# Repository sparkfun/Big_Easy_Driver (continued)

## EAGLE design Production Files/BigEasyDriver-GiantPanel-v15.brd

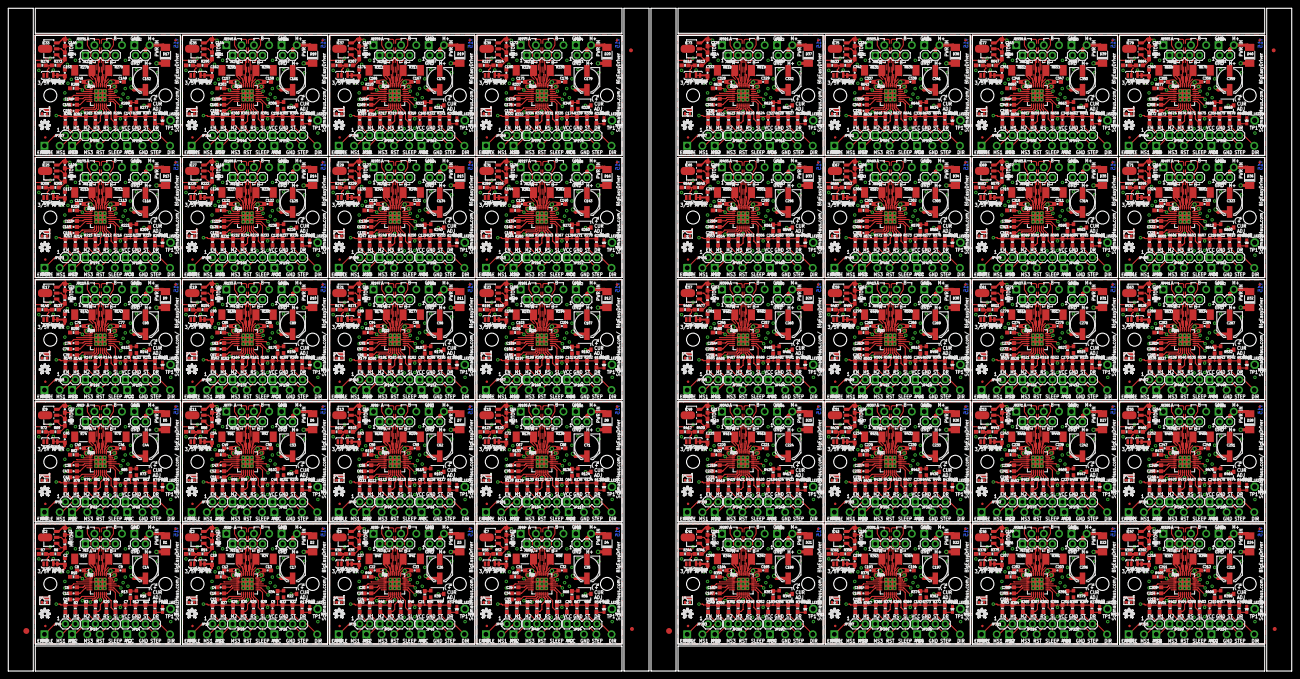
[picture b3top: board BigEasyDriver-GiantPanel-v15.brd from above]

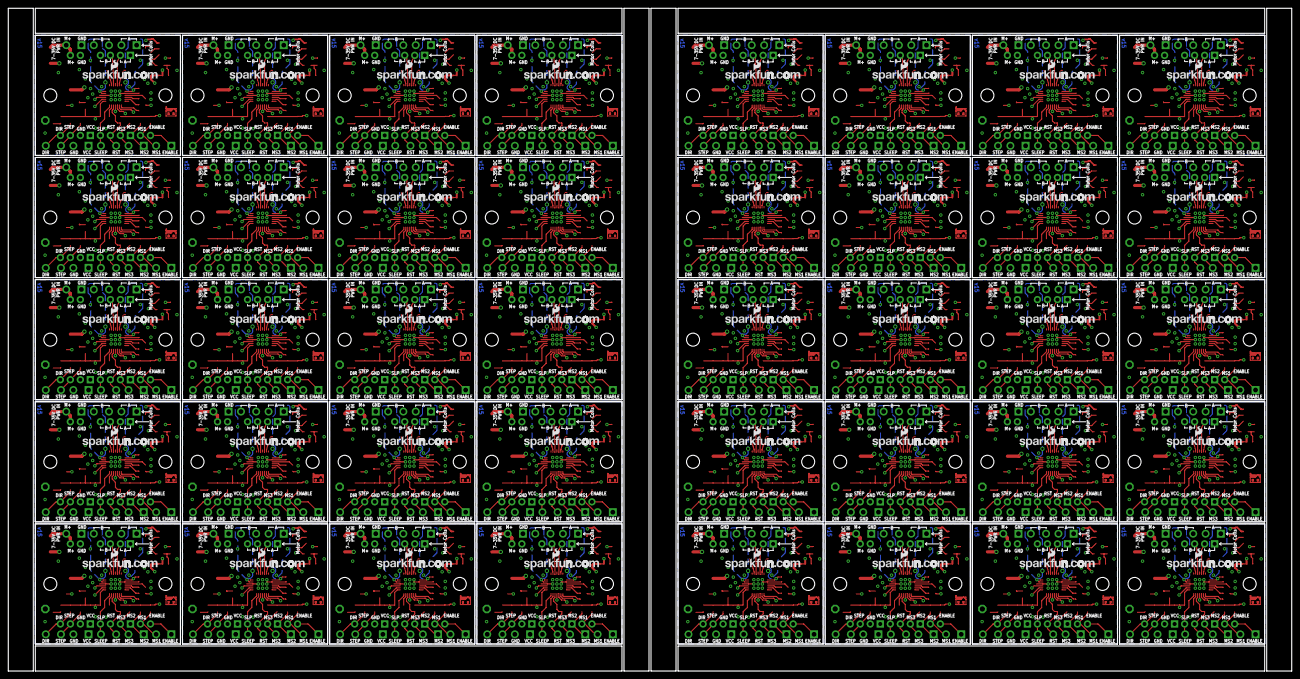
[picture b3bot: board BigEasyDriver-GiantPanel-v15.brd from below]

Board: 2 copper layers, 325.6 x 168.1 mm, 2126 parts (40 on the bottom side), 1280 nets.

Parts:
3/5V, 3/5V1, 3/5V2, 3/5V3, 3/5V4, 3/5V5, 3/5V6, 3/5V7, 3/5V8, 3/5V9, 3/5V10, 3/5V11, 3/5V12, 3/5V13, 3/5V14, 3/5V15, 3/5V16, 3/5V17, 3/5V18, 3/5V19, 3/5V20, 3/5V21, 3/5V22, 3/5V23, 3/5V24, 3/5V25, 3/5V26, 3/5V27, 3/5V28, 3/5V29, 3/5V30, 3/5V31, 3/5V32, 3/5V33, 3/5V34, 3/5V35, 3/5V36, 3/5V37, 3/5V38, 3/5V39: SOLDERJUMPERNO; SJ_2S-NO
APWR, APWR1, APWR2, APWR3, APWR4, APWR5, APWR6, APWR7, APWR8, APWR9, APWR10, APWR11, APWR12, APWR13, APWR14, APWR15, APWR16, APWR17, APWR18, APWR19, APWR20, APWR21, APWR22, APWR23, APWR24, APWR25, APWR26, APWR27, APWR28, APWR29, APWR30, APWR31, APWR32, APWR33, APWR34, APWR35, APWR36, APWR37, APWR38, APWR39: SOLDERJUMPERTRACE; SJ_2S-TRACE
C1, C3, C19, C28, C37, C46, C55, C64, C73, C82, C91, C100, C109, C118, C127, C136, C145, C154, C163, C172, C181, C190, C199, C208, C217, C226, C235, C244, C253, C262, C271, C280, C289, C298, C307, C316, C325, C334, C343, C352: .1uF; 0603-CAP
C2, C18, C27, C36, C45, C54, C63, C72, C81, C90, C99, C108, C117, C126, C135, C144, C153, C162, C171, C180, C189, C198, C207, C216, C225, C234, C243, C252, C261, C270, C279, C288, C297, C306, C315, C324, C333, C342, C351, C360: 1uF; 0603-CAP
C4, C5, C6, C7, C8, C9, C11, C12, C13, C16, C20, C21, C22, C23, C25, C29, C30, C31, C32, C34, C38, C39, C40, C41, C43, C47, C48, C49, C50, C52, C56, C57, C58, C59, C61, C65, C66, C67, C68, C70, C74, C75, C76, C77, C79, C83, C84, C85, C86, C88, C92, C93, C94, C95, C97, C101, C102, C103, C104, C106, C110, C111, C112, C113, C115, C119, C120, C121, C122, C124, C128, C129, C130, C131, C133, C137, C138, C139, C140, C142, C146, C147, C148, C149, C151, C155, C156, C157, C158, C160, C164, C165, C166, C167, C169, C173, C174, C175, C176, C178, C182, C183, C184, C185, C187, C191, C192, C193, C194, C196, C200, C201, C202, C203, C205, C209, C210, C211, C212, C214, C218, C219, C220, C221, C223, C227, C228, C229, C230, C232, C236, C237, C238, C239, C241, C245, C246, C247, C248, C250, C254, C255, C256, C257, C259, C263, C264, C265, C266, C268, C272, C273, C274, C275, C277, C281, C282, C283, C284, C286, C290, C291, C292, C293, C295, C299, C300, C301, C302, C304, C308, C309, C310, C311, C313, C317, C318, C319, C320, C322, C326, C327, C328, C329, C331, C335, C336, C337, C338, C340, C344, C345, C346, C347, C349, C353, C354, C355, C356, C358: .1uf; 0603-CAP
C10, C15, C24, C33, C42, C51, C60, C69, C78, C87, C96, C105, C114, C123, C132, C141, C150, C159, C168, C177, C186, C195, C204, C213, C222, C231, C240, C249, C258, C267, C276, C285, C294, C303, C312, C321, C330, C339, C348, C357: .22uF; 0603-CAP
C14, C17, C26, C35, C44, C53, C62, C71, C80, C89, C98, C107, C116, C125, C134, C143, C152, C161, C170, C179, C188, C197, C206, C215, C224, C233, C242, C251, C260, C269, C278, C287, C296, C305, C314, C323, C332, C341, C350, C359: 47uF; PANASONIC_D
D1, D2, D3, D4, D5, D6, D7, D8, D9, D10, D11, D12, D13, D14, D15, D16, D17, D18, D19, D20, D21, D22, D23, D24, D25, D26, D27, D28, D29, D30, D31, D32, D33, D34, D35, D36, D37, D38, D39, D40: B340A-13-F; DO-214AC
E$1, E$5: FIDUCIAL-1.5X3
E$2, E$3, E$4, E$6: FIDUCIAL-1X2
IC1, IC4, IC6, IC8, IC10, IC12, IC14, IC16, IC18, IC20, IC22, IC24, IC26, IC28, IC30, IC32, IC34, IC36, IC38, IC40, IC42, IC44, IC46, IC48, IC50, IC52, IC54, IC56, IC58, IC60, IC62, IC64, IC66, IC68, IC70, IC72, IC74, IC76, IC78, IC80: A4983ALT1; QFN-28-5MM_ALT1
IC2, IC3, IC5, IC7, IC9, IC11, IC13, IC15, IC17, IC19, IC21, IC23, IC25, IC27, IC29, IC31, IC33, IC35, IC37, IC39, IC41, IC43, IC45, IC47, IC49, IC51, IC53, IC55, IC57, IC59, IC61, IC63, IC65, IC67, IC69, IC71, IC73, IC75, IC77, IC79: LM317L; SCHMALZHAUS_SOT89
JP1, JP6, JP17, JP19, JP31, JP33, JP45, JP47, JP59, JP61, JP73, JP75, JP87, JP89, JP101, JP103, JP115, JP117, JP129, JP131, JP143, JP145, JP157, JP159, JP171, JP173, JP185, JP187, JP199, JP201, JP213, JP215, JP227, JP229, JP241, JP243, JP255, JP257, JP269, JP271, JP283, JP285, JP297, JP299, JP311, JP313, JP325, JP327, JP339, JP341, JP353, JP355, JP367, JP369, JP381, JP383, JP395, JP397, JP409, JP411, JP423, JP425, JP437, JP439, JP451, JP453, JP465, JP467, JP479, JP481, JP493, JP495, JP507, JP509, JP521, JP523, JP535, JP537, JP549, JP551: 1X02
JP2, JP4, JP27, JP28, JP41, JP42, JP55, JP56, JP69, JP70, JP83, JP84, JP97, JP98, JP111, JP112, JP125, JP126, JP139, JP140, JP153, JP154, JP167, JP168, JP181, JP182, JP195, JP196, JP209, JP210, JP223, JP224, JP237, JP238, JP251, JP252, JP265, JP266, JP279, JP280, JP293, JP294, JP307, JP308, JP321, JP322, JP335, JP336, JP349, JP350, JP363, JP364, JP377, JP378, JP391, JP392, JP405, JP406, JP419, JP420, JP433, JP434, JP447, JP448, JP461, JP462, JP475, JP476, JP489, JP490, JP503, JP504, JP517, JP518, JP531, JP532, JP545, JP546, JP559, JP560: FIDUCIAL1X2.5; FIDUCIAL-1X2.5
JP3, JP10, JP14, JP18, JP20, JP26, JP32, JP34, JP40, JP46, JP48, JP54, JP60, JP62, JP68, JP74, JP76, JP82, JP88, JP90, JP96, JP102, JP104, JP110, JP116, JP118, JP124, JP130, JP132, JP138, JP144, JP146, JP152, JP158, JP160, JP166, JP172, JP174, JP180, JP186, JP188, JP194, JP200, JP202, JP208, JP214, JP216, JP222, JP228, JP230, JP236, JP242, JP244, JP250, JP256, JP258, JP264, JP270, JP272, JP278, JP284, JP286, JP292, JP298, JP300, JP306, JP312, JP314, JP320, JP326, JP328, JP334, JP340, JP342, JP348, JP354, JP356, JP362, JP368, JP370, JP376, JP382, JP384, JP390, JP396, JP398, JP404, JP410, JP412, JP418, JP424, JP426, JP432, JP438, JP440, JP446, JP452, JP454, JP460, JP466, JP468, JP474, JP480, JP482, JP488, JP494, JP496, JP502, JP508, JP510, JP516, JP522, JP524, JP530, JP536, JP538, JP544, JP550, JP552, JP558: 1X04
JP5, JP11, JP12, JP21, JP23, JP24, JP35, JP37, JP38, JP49, JP51, JP52, JP63, JP65, JP66, JP77, JP79, JP80, JP91, JP93, JP94, JP105, JP107, JP108, JP119, JP121, JP122, JP133, JP135, JP136, JP147, JP149, JP150, JP161, JP163, JP164, JP175, JP177, JP178, JP189, JP191, JP192, JP203, JP205, JP206, JP217, JP219, JP220, JP231, JP233, JP234, JP245, JP247, JP248, JP259, JP261, JP262, JP273, JP275, JP276, JP287, JP289, JP290, JP301, JP303, JP304, JP315, JP317, JP318, JP329, JP331, JP332, JP343, JP345, JP346, JP357, JP359, JP360, JP371, JP373, JP374, JP385, JP387, JP388, JP399, JP401, JP402, JP413, JP415, JP416, JP427, JP429, JP430, JP441, JP443, JP444, JP455, JP457, JP458, JP469, JP471, JP472, JP483, JP485, JP486, JP497, JP499, JP500, JP511, JP513, JP514, JP525, JP527, JP528, JP539, JP541, JP542, JP553, JP555, JP556: SCREWTERMINAL-3.5MM-4_LOCK
JP7, JP13, JP22, JP25, JP36, JP39, JP50, JP53, JP64, JP67, JP78, JP81, JP92, JP95, JP106, JP109, JP120, JP123, JP134, JP137, JP148, JP151, JP162, JP165, JP176, JP179, JP190, JP193, JP204, JP207, JP218, JP221, JP232, JP235, JP246, JP249, JP260, JP263, JP274, JP277, JP288, JP291, JP302, JP305, JP316, JP319, JP330, JP333, JP344, JP347, JP358, JP361, JP372, JP375, JP386, JP389, JP400, JP403, JP414, JP417, JP428, JP431, JP442, JP445, JP456, JP459, JP470, JP473, JP484, JP487, JP498, JP501, JP512, JP515, JP526, JP529, JP540, JP543, JP554, JP557: SCREWTERMINAL-3.5MM-2_LOCK
JP8, JP9, JP15, JP16, JP29, JP30, JP43, JP44, JP57, JP58, JP71, JP72, JP85, JP86, JP99, JP100, JP113, JP114, JP127, JP128, JP141, JP142, JP155, JP156, JP169, JP170, JP183, JP184, JP197, JP198, JP211, JP212, JP225, JP226, JP239, JP240, JP253, JP254, JP267, JP268, JP281, JP282, JP295, JP296, JP309, JP310, JP323, JP324, JP337, JP338, JP351, JP352, JP365, JP366, JP379, JP380, JP393, JP394, JP407, JP408, JP421, JP422, JP435, JP436, JP449, JP450, JP463, JP464, JP477, JP478, JP491, JP492, JP505, JP506, JP519, JP520, JP533, JP534, JP547, JP548: STAND-OFF
LOGO1, LOGO2, LOGO3, LOGO4, LOGO5, LOGO6, LOGO7, LOGO8, LOGO9, LOGO10, LOGO11, LOGO12, LOGO13, LOGO14, LOGO15, LOGO16, LOGO17, LOGO18, LOGO19, LOGO20, LOGO21, LOGO22, LOGO23, LOGO24, LOGO25, LOGO26, LOGO27, LOGO28, LOGO29, LOGO30, LOGO31, LOGO32, LOGO33, LOGO34, LOGO35, LOGO36, LOGO37, LOGO38, LOGO39, LOGO40: OSHW_LOGO_FILLX0100-NT; OSHW_FILLX100_NOTEXT
PWR_LED, PWR_LED1, PWR_LED2, PWR_LED3, PWR_LED4, PWR_LED5, PWR_LED6, PWR_LED7, PWR_LED8, PWR_LED9, PWR_LED10, PWR_LED11, PWR_LED12, PWR_LED13, PWR_LED14, PWR_LED15, PWR_LED16, PWR_LED17, PWR_LED18, PWR_LED19, PWR_LED20, PWR_LED21, PWR_LED22, PWR_LED23, PWR_LED24, PWR_LED25, PWR_LED26, PWR_LED27, PWR_LED28, PWR_LED29, PWR_LED30, PWR_LED31, PWR_LED32, PWR_LED33, PWR_LED34, PWR_LED35, PWR_LED36, PWR_LED37, PWR_LED38, PWR_LED39: YELLOW; LED-0603
R1, R2, R3, R4, R5, R10, R11, R12, R20, R25, R26, R27, R28, R29, R30, R31, R32, R33, R42, R43, R44, R45, R46, R47, R48, R49, R50, R59, R60, R61, R62, R63, R64, R65, R66, R67, R76, R77, R78, R79, R80, R81, R82, R83, R84, R93, R94, R95, R96, R97, R98, R99, R100, R101, R110, R111, R112, R113, R114, R115, R116, R117, R118, R127, R128, R129, R130, R131, R132, R133, R134, R135, R144, R145, R146, R147, R148, R149, R150, R151, R152, R161, R162, R163, R164, R165, R166, R167, R168, R169, R178, R179, R180, R181, R182, R183, R184, R185, R186, R195, R196, R197, R198, R199, R200, R201, R202, R203, R212, R213, R214, R215, R216, R217, R218, R219, R220, R229, R230, R231, R232, R233, R234, R235, R236, R237, R246, R247, R248, R249, R250, R251, R252, R253, R254, R263, R264, R265, R266, R267, R268, R269, R270, R271, R280, R281, R282, R283, R284, R285, R286, R287, R288, R297, R298, R299, R300, R301, R302, R303, R304, R305, R314, R315, R316, R317, R318, R319, R320, R321, R322, R331, R332, R333, R334, R335, R336, R337, R338, R339, R348, R349, R350, R351, R352, R353, R354, R355, R356, R365, R366, R367, R368, R369, R370, R371, R372, R373, R382, R383, R384, R385, R386, R387, R388, R389, R390, R399, R400, R401, R402, R403, R404, R405, R406, R407, R416, R417, R418, R419, R420, R421, R422, R423, R424, R433, R434, R435, R436, R437, R438, R439, R440, R441, R450, R451, R452, R453, R454, R455, R456, R457, R458, R467, R468, R469, R470, R471, R472, R473, R474, R475, R484, R485, R486, R487, R488, R489, R490, R491, R492, R501, R502, R503, R504, R505, R506, R507, R508, R509, R518, R519, R520, R521, R522, R523, R524, R525, R526, R535, R536, R537, R538, R539, R540, R541, R542, R543, R552, R553, R554, R555, R556, R557, R558, R559, R560, R569, R570, R571, R572, R573, R574, R575, R576, R577, R586, R587, R588, R589, R590, R591, R592, R593, R594, R603, R604, R605, R606, R607, R608, R609, R610, R611, R620, R621, R622, R623, R624, R625, R626, R627, R628, R637, R638, R639, R640, R641, R642, R643, R644, R645, R654, R655, R656, R657, R658, R659, R660, R661, R662, R671, R672, R673, R674, R675, R676, R677, R678, R679: 20K; 0603-RES
R6, R14, R35, R52, R69, R86, R103, R120, R137, R154, R171, R188, R205, R222, R239, R256, R273, R290, R307, R324, R341, R358, R375, R392, R409, R426, R443, R460, R477, R494, R511, R528, R545, R562, R579, R596, R613, R630, R647, R664: 390; 0603-RES
R7, R21, R38, R55, R72, R89, R106, R123, R140, R157, R174, R191, R208, R225, R242, R259, R276, R293, R310, R327, R344, R361, R378, R395, R412, R429, R446, R463, R480, R497, R514, R531, R548, R565, R582, R599, R616, R633, R650, R667: 330; 0603-RES
R8, R15, R36, R53, R70, R87, R104, R121, R138, R155, R172, R189, R206, R223, R240, R257, R274, R291, R308, R325, R342, R359, R376, R393, R410, R427, R444, R461, R478, R495, R512, R529, R546, R563, R580, R597, R614, R631, R648, R665: 240; 0603-RES
R9, R17, R37, R54, R71, R88, R105, R122, R139, R156, R173, R190, R207, R224, R241, R258, R275, R292, R309, R326, R343, R360, R377, R394, R411, R428, R445, R462, R479, R496, R513, R530, R547, R564, R581, R598, R615, R632, R649, R666: 1K; 0603-RES
R13, R34, R51, R68, R85, R102, R119, R136, R153, R170, R187, R204, R221, R238, R255, R272, R289, R306, R323, R340, R357, R374, R391, R408, R425, R442, R459, R476, R493, R510, R527, R544, R561, R578, R595, R612, R629, R646, R663, R680: 2.49K; 0603-RES
R16, R22, R39, R56, R73, R90, R107, R124, R141, R158, R175, R192, R209, R226, R243, R260, R277, R294, R311, R328, R345, R362, R379, R396, R413, R430, R447, R464, R481, R498, R515, R532, R549, R566, R583, R600, R617, R634, R651, R668: 10K; TRIMPOT-3MM
R18, R19, R23, R24, R40, R41, R57, R58, R74, R75, R91, R92, R108, R109, R125, R126, R142, R143, R159, R160, R176, R177, R193, R194, R210, R211, R227, R228, R244, R245, R261, R262, R278, R279, R295, R296, R312, R313, R329, R330, R346, R347, R363, R364, R380, R381, R397, R398, R414, R415, R431, R432, R448, R449, R465, R466, R482, R483, R499, R500, R516, R517, R533, R534, R550, R551, R567, R568, R584, R585, R601, R602, R618, R619, R635, R636, R652, R653, R669, R670: .11; R2010
TP1, TP2, TP3, TP4, TP5, TP6, TP7, TP8, TP9, TP10, TP11, TP12, TP13, TP14, TP15, TP16, TP17, TP18, TP19, TP20, TP21, TP22, TP23, TP24, TP25, TP26, TP27, TP28, TP29, TP30, TP31, TP32, TP33, TP34, TP35, TP36, TP37, TP38, TP39, TP40: TPPAD1-13; P1-13
U$1, U$6, U$11, U$16, U$21, U$26, U$31, U$36, U$41, U$46, U$51, U$56, U$61, U$66, U$71, U$76, U$81, U$86, U$91, U$96, U$101, U$106, U$111, U$116, U$121, U$126, U$131, U$136, U$141, U$146, U$151, U$156, U$161, U$166, U$171, U$176, U$181, U$186, U$191, U$196: SCHMALZHAUS_SMALL
U$2, U$7, U$12, U$17, U$22, U$27, U$32, U$37, U$42, U$47, U$52, U$57, U$62, U$67, U$72, U$77, U$82, U$87, U$92, U$97, U$102, U$107, U$112, U$117, U$122, U$127, U$132, U$137, U$142, U$147, U$152, U$157, U$162, U$167, U$172, U$177, U$182, U$187, U$192, U$197: LOGO-SFENEW; SFE-NEW-WEBLOGO
U$3, U$4, U$5, U$8, U$9, U$10, U$13, U$14, U$15, U$18, U$19, U$20, U$23, U$24, U$25, U$28, U$29, U$30, U$33, U$34, U$35, U$38, U$39, U$40, U$43, U$44, U$45, U$48, U$49, U$50, U$53, U$54, U$55, U$58, U$59, U$60, U$63, U$64, U$65, U$68, U$69, U$70, U$73, U$74, U$75, U$78, U$79, U$80, U$83, U$84, U$85, U$88, U$89, U$90, U$93, U$94, U$95, U$98, U$99, U$100, U$103, U$104, U$105, U$108, U$109, U$110, U$113, U$114, U$115, U$118, U$119, U$120, U$123, U$124, U$125, U$128, U$129, U$130, U$133, U$134, U$135, U$138, U$139, U$140, U$143, U$144, U$145, U$148, U$149, U$150, U$153, U$154, U$155, U$158, U$159, U$160, U$163, U$164, U$165, U$168, U$169, U$170, U$173, U$174, U$175, U$178, U$179, U$180, U$183, U$184, U$185, U$188, U$189, U$190, U$193, U$194, U$195, U$198, U$199, U$200: PAD; PAD-0.008

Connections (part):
5V_ALT: APWR.1, IC2.OUT, IC2.OUT@1, R8.2
5V_ALT1: APWR1.1, IC3.OUT, IC3.OUT@1, R15.2
5V_ALT2: APWR2.1, IC5.OUT, IC5.OUT@1, R36.2
5V_ALT3: APWR3.1, IC7.OUT, IC7.OUT@1, R53.2
5V_ALT4: APWR4.1, IC9.OUT, IC9.OUT@1, R70.2
5V_ALT5: APWR5.1, IC11.OUT, IC11.OUT@1, R87.2
5V_ALT6: APWR6.1, IC13.OUT, IC13.OUT@1, R104.2
5V_ALT7: APWR7.1, IC15.OUT, IC15.OUT@1, R121.2
5V_ALT8: APWR8.1, IC17.OUT, IC17.OUT@1, R138.2
5V_ALT9: APWR9.1, IC19.OUT, IC19.OUT@1, R155.2
5V_ALT10: APWR10.1, IC21.OUT, IC21.OUT@1, R172.2
5V_ALT11: APWR11.1, IC23.OUT, IC23.OUT@1, R189.2
5V_ALT12: APWR12.1, IC25.OUT, IC25.OUT@1, R206.2
5V_ALT13: APWR13.1, IC27.OUT, IC27.OUT@1, R223.2
5V_ALT14: APWR14.1, IC29.OUT, IC29.OUT@1, R240.2
5V_ALT15: APWR15.1, IC31.OUT, IC31.OUT@1, R257.2
5V_ALT16: APWR16.1, IC33.OUT, IC33.OUT@1, R274.2
5V_ALT17: APWR17.1, IC35.OUT, IC35.OUT@1, R291.2
5V_ALT18: APWR18.1, IC37.OUT, IC37.OUT@1, R308.2
5V_ALT19: APWR19.1, IC39.OUT, IC39.OUT@1, R325.2
5V_ALT20: APWR20.1, IC41.OUT, IC41.OUT@1, R342.2
5V_ALT21: APWR21.1, IC43.OUT, IC43.OUT@1, R359.2
5V_ALT22: APWR22.1, IC45.OUT, IC45.OUT@1, R376.2
5V_ALT23: APWR23.1, IC47.OUT, IC47.OUT@1, R393.2
5V_ALT24: APWR24.1, IC49.OUT, IC49.OUT@1, R410.2
5V_ALT25: APWR25.1, IC51.OUT, IC51.OUT@1, R427.2
5V_ALT26: APWR26.1, IC53.OUT, IC53.OUT@1, R444.2
5V_ALT27: APWR27.1, IC55.OUT, IC55.OUT@1, R461.2
5V_ALT28: APWR28.1, IC57.OUT, IC57.OUT@1, R478.2
5V_ALT29: APWR29.1, IC59.OUT, IC59.OUT@1, R495.2
5V_ALT30: APWR30.1, IC61.OUT, IC61.OUT@1, R512.2
5V_ALT31: APWR31.1, IC63.OUT, IC63.OUT@1, R529.2
5V_ALT32: APWR32.1, IC65.OUT, IC65.OUT@1, R546.2
5V_ALT33: APWR33.1, IC67.OUT, IC67.OUT@1, R563.2
5V_ALT34: APWR34.1, IC69.OUT, IC69.OUT@1, R580.2
5V_ALT35: APWR35.1, IC71.OUT, IC71.OUT@1, R597.2
5V_ALT36: APWR36.1, IC73.OUT, IC73.OUT@1, R614.2
5V_ALT37: APWR37.1, IC75.OUT, IC75.OUT@1, R631.2
5V_ALT38: APWR38.1, IC77.OUT, IC77.OUT@1, R648.2
5V_ALT39: APWR39.1, IC79.OUT, IC79.OUT@1, R665.2
COILA+: IC1.P$21, JP3.4, JP5.4
COILA+1: IC4.P$21, JP18.4, JP21.4
COILA+2: IC6.P$21, JP32.4, JP35.4
COILA+3: IC8.P$21, JP46.4, JP49.4
COILA+4: IC10.P$21, JP60.4, JP63.4
COILA+5: IC12.P$21, JP74.4, JP77.4
COILA+6: IC14.P$21, JP88.4, JP91.4
COILA+7: IC16.P$21, JP102.4, JP105.4
COILA+8: IC18.P$21, JP116.4, JP119.4
COILA+9: IC20.P$21, JP130.4, JP133.4
COILA+10: IC22.P$21, JP144.4, JP147.4
COILA+11: IC24.P$21, JP158.4, JP161.4
COILA+12: IC26.P$21, JP172.4, JP175.4
COILA+13: IC28.P$21, JP186.4, JP189.4
COILA+14: IC30.P$21, JP200.4, JP203.4
COILA+15: IC32.P$21, JP214.4, JP217.4
COILA+16: IC34.P$21, JP228.4, JP231.4
COILA+17: IC36.P$21, JP242.4, JP245.4
COILA+18: IC38.P$21, JP256.4, JP259.4
COILA+19: IC40.P$21, JP270.4, JP273.4
COILA+20: IC42.P$21, JP284.4, JP287.4
COILA+21: IC44.P$21, JP298.4, JP301.4
COILA+22: IC46.P$21, JP312.4, JP315.4
COILA+23: IC48.P$21, JP326.4, JP329.4
COILA+24: IC50.P$21, JP340.4, JP343.4
COILA+25: IC52.P$21, JP354.4, JP357.4
COILA+26: IC54.P$21, JP368.4, JP371.4
COILA+27: IC56.P$21, JP382.4, JP385.4
COILA+28: IC58.P$21, JP396.4, JP399.4
COILA+29: IC60.P$21, JP410.4, JP413.4
COILA+30: IC62.P$21, JP424.4, JP427.4
COILA+31: IC64.P$21, JP438.4, JP441.4
COILA+32: IC66.P$21, JP452.4, JP455.4
COILA+33: IC68.P$21, JP466.4, JP469.4
COILA+34: IC70.P$21, JP480.4, JP483.4
COILA+35: IC72.P$21, JP494.4, JP497.4
COILA+36: IC74.P$21, JP508.4, JP511.4
COILA+37: IC76.P$21, JP522.4, JP525.4
COILA+38: IC78.P$21, JP536.4, JP539.4
COILA+39: IC80.P$21, JP550.4, JP553.4
COILA-: IC1.P$24, JP3.3, JP5.3
COILA-1: IC4.P$24, JP18.3, JP21.3
COILA-2: IC6.P$24, JP32.3, JP35.3
COILA-3: IC8.P$24, JP46.3, JP49.3
COILA-4: IC10.P$24, JP60.3, JP63.3
COILA-5: IC12.P$24, JP74.3, JP77.3
COILA-6: IC14.P$24, JP88.3, JP91.3
COILA-7: IC16.P$24, JP102.3, JP105.3
COILA-8: IC18.P$24, JP116.3, JP119.3
COILA-9: IC20.P$24, JP130.3, JP133.3
COILA-10: IC22.P$24, JP144.3, JP147.3
COILA-11: IC24.P$24, JP158.3, JP161.3
COILA-12: IC26.P$24, JP172.3, JP175.3
COILA-13: IC28.P$24, JP186.3, JP189.3
COILA-14: IC30.P$24, JP200.3, JP203.3
COILA-15: IC32.P$24, JP214.3, JP217.3
COILA-16: IC34.P$24, JP228.3, JP231.3
COILA-17: IC36.P$24, JP242.3, JP245.3
COILA-18: IC38.P$24, JP256.3, JP259.3
COILA-19: IC40.P$24, JP270.3, JP273.3
COILA-20: IC42.P$24, JP284.3, JP287.3
COILA-21: IC44.P$24, JP298.3, JP301.3
COILA-22: IC46.P$24, JP312.3, JP315.3
COILA-23: IC48.P$24, JP326.3, JP329.3
COILA-24: IC50.P$24, JP340.3, JP343.3
COILA-25: IC52.P$24, JP354.3, JP357.3
COILA-26: IC54.P$24, JP368.3, JP371.3
COILA-27: IC56.P$24, JP382.3, JP385.3
COILA-28: IC58.P$24, JP396.3, JP399.3
COILA-29: IC60.P$24, JP410.3, JP413.3
COILA-30: IC62.P$24, JP424.3, JP427.3
COILA-31: IC64.P$24, JP438.3, JP441.3
COILA-32: IC66.P$24, JP452.3, JP455.3
COILA-33: IC68.P$24, JP466.3, JP469.3
COILA-34: IC70.P$24, JP480.3, JP483.3
COILA-35: IC72.P$24, JP494.3, JP497.3
COILA-36: IC74.P$24, JP508.3, JP511.3
COILA-37: IC76.P$24, JP522.3, JP525.3
COILA-38: IC78.P$24, JP536.3, JP539.3
COILA-39: IC80.P$24, JP550.3, JP553.3
COILB+: IC1.P$1, JP3.1, JP5.1
COILB+1: IC4.P$1, JP18.1, JP21.1
COILB+2: IC6.P$1, JP32.1, JP35.1
COILB+3: IC8.P$1, JP46.1, JP49.1
COILB+4: IC10.P$1, JP60.1, JP63.1
COILB+5: IC12.P$1, JP74.1, JP77.1
COILB+6: IC14.P$1, JP88.1, JP91.1
COILB+7: IC16.P$1, JP102.1, JP105.1
COILB+8: IC18.P$1, JP116.1, JP119.1
COILB+9: IC20.P$1, JP130.1, JP133.1
COILB+10: IC22.P$1, JP144.1, JP147.1
COILB+11: IC24.P$1, JP158.1, JP161.1
COILB+12: IC26.P$1, JP172.1, JP175.1
COILB+13: IC28.P$1, JP186.1, JP189.1
COILB+14: IC30.P$1, JP200.1, JP203.1
COILB+15: IC32.P$1, JP214.1, JP217.1
COILB+16: IC34.P$1, JP228.1, JP231.1
COILB+17: IC36.P$1, JP242.1, JP245.1
COILB+18: IC38.P$1, JP256.1, JP259.1
COILB+19: IC40.P$1, JP270.1, JP273.1
COILB+20: IC42.P$1, JP284.1, JP287.1
COILB+21: IC44.P$1, JP298.1, JP301.1
COILB+22: IC46.P$1, JP312.1, JP315.1
COILB+23: IC48.P$1, JP326.1, JP329.1
COILB+24: IC50.P$1, JP340.1, JP343.1
COILB+25: IC52.P$1, JP354.1, JP357.1
COILB+26: IC54.P$1, JP368.1, JP371.1
COILB+27: IC56.P$1, JP382.1, JP385.1
COILB+28: IC58.P$1, JP396.1, JP399.1
COILB+29: IC60.P$1, JP410.1, JP413.1
COILB+30: IC62.P$1, JP424.1, JP427.1
COILB+31: IC64.P$1, JP438.1, JP441.1
COILB+32: IC66.P$1, JP452.1, JP455.1
COILB+33: IC68.P$1, JP466.1, JP469.1
COILB+34: IC70.P$1, JP480.1, JP483.1
COILB+35: IC72.P$1, JP494.1, JP497.1
COILB+36: IC74.P$1, JP508.1, JP511.1
COILB+37: IC76.P$1, JP522.1, JP525.1
COILB+38: IC78.P$1, JP536.1, JP539.1
COILB+39: IC80.P$1, JP550.1, JP553.1
COILB-: IC1.P$26, JP3.2, JP5.2
COILB-1: IC4.P$26, JP18.2, JP21.2
COILB-2: IC6.P$26, JP32.2, JP35.2
COILB-3: IC8.P$26, JP46.2, JP49.2
COILB-4: IC10.P$26, JP60.2, JP63.2
COILB-5: IC12.P$26, JP74.2, JP77.2
COILB-6: IC14.P$26, JP88.2, JP91.2
COILB-7: IC16.P$26, JP102.2, JP105.2
COILB-8: IC18.P$26, JP116.2, JP119.2
COILB-9: IC20.P$26, JP130.2, JP133.2
COILB-10: IC22.P$26, JP144.2, JP147.2
COILB-11: IC24.P$26, JP158.2, JP161.2
COILB-12: IC26.P$26, JP172.2, JP175.2
COILB-13: IC28.P$26, JP186.2, JP189.2
COILB-14: IC30.P$26, JP200.2, JP203.2
COILB-15: IC32.P$26, JP214.2, JP217.2
COILB-16: IC34.P$26, JP228.2, JP231.2
COILB-17: IC36.P$26, JP242.2, JP245.2
COILB-18: IC38.P$26, JP256.2, JP259.2
COILB-19: IC40.P$26, JP270.2, JP273.2
COILB-20: IC42.P$26, JP284.2, JP287.2
COILB-21: IC44.P$26, JP298.2, JP301.2
COILB-22: IC46.P$26, JP312.2, JP315.2
COILB-23: IC48.P$26, JP326.2, JP329.2
COILB-24: IC50.P$26, JP340.2, JP343.2
COILB-25: IC52.P$26, JP354.2, JP357.2
COILB-26: IC54.P$26, JP368.2, JP371.2
COILB-27: IC56.P$26, JP382.2, JP385.2
COILB-28: IC58.P$26, JP396.2, JP399.2
COILB-29: IC60.P$26, JP410.2, JP413.2
COILB-30: IC62.P$26, JP424.2, JP427.2
COILB-31: IC64.P$26, JP438.2, JP441.2
COILB-32: IC66.P$26, JP452.2, JP455.2
COILB-33: IC68.P$26, JP466.2, JP469.2
COILB-34: IC70.P$26, JP480.2, JP483.2
COILB-35: IC72.P$26, JP494.2, JP497.2
COILB-36: IC74.P$26, JP508.2, JP511.2
COILB-37: IC76.P$26, JP522.2, JP525.2
COILB-38: IC78.P$26, JP536.2, JP539.2
COILB-39: IC80.P$26, JP550.2, JP553.2
CUR_REF: IC1.P$17, R16.2, TP1.TP
CUR_REF1: IC4.P$17, R22.2, TP2.TP
CUR_REF2: IC6.P$17, R39.2, TP3.TP
CUR_REF3: IC8.P$17, R56.2, TP4.TP
CUR_REF4: IC10.P$17, R73.2, TP5.TP
CUR_REF5: IC12.P$17, R90.2, TP6.TP
CUR_REF6: IC14.P$17, R107.2, TP7.TP
CUR_REF7: IC16.P$17, R124.2, TP8.TP
CUR_REF8: IC18.P$17, R141.2, TP9.TP
CUR_REF9: IC20.P$17, R158.2, TP10.TP
CUR_REF10: IC22.P$17, R175.2, TP11.TP
CUR_REF11: IC24.P$17, R192.2, TP12.TP
CUR_REF12: IC26.P$17, R209.2, TP13.TP
CUR_REF13: IC28.P$17, R226.2, TP14.TP
CUR_REF14: IC30.P$17, R243.2, TP15.TP
CUR_REF15: IC32.P$17, R260.2, TP16.TP
CUR_REF16: IC34.P$17, R277.2, TP17.TP
CUR_REF17: IC36.P$17, R294.2, TP18.TP
CUR_REF18: IC38.P$17, R311.2, TP19.TP
CUR_REF19: IC40.P$17, R328.2, TP20.TP
CUR_REF20: IC42.P$17, R345.2, TP21.TP
CUR_REF21: IC44.P$17, R362.2, TP22.TP
CUR_REF22: IC46.P$17, R379.2, TP23.TP
CUR_REF23: IC48.P$17, R396.2, TP24.TP
CUR_REF24: IC50.P$17, R413.2, TP25.TP
CUR_REF25: IC52.P$17, R430.2, TP26.TP
CUR_REF26: IC54.P$17, R447.2, TP27.TP
CUR_REF27: IC56.P$17, R464.2, TP28.TP
CUR_REF28: IC58.P$17, R481.2, TP29.TP
CUR_REF29: IC60.P$17, R498.2, TP30.TP
CUR_REF30: IC62.P$17, R515.2, TP31.TP
CUR_REF31: IC64.P$17, R532.2, TP32.TP
CUR_REF32: IC66.P$17, R549.2, TP33.TP
CUR_REF33: IC68.P$17, R566.2, TP34.TP
CUR_REF34: IC70.P$17, R583.2, TP35.TP
CUR_REF35: IC72.P$17, R600.2, TP36.TP
CUR_REF36: IC74.P$17, R617.2, TP37.TP
CUR_REF37: IC76.P$17, R634.2, TP38.TP
CUR_REF38: IC78.P$17, R651.2, TP39.TP
CUR_REF39: IC80.P$17, R668.2, TP40.TP
DIR: IC1.P$19, JP12.4, JP14.4, R11.1
DIR1: IC4.P$19, JP24.4, JP26.4, R32.1
DIR2: IC6.P$19, JP38.4, JP40.4, R49.1
DIR3: IC8.P$19, JP52.4, JP54.4, R66.1
DIR4: IC10.P$19, JP66.4, JP68.4, R83.1
DIR5: IC12.P$19, JP80.4, JP82.4, R100.1
DIR6: IC14.P$19, JP94.4, JP96.4, R117.1
DIR7: IC16.P$19, JP108.4, JP110.4, R134.1
DIR8: IC18.P$19, JP122.4, JP124.4, R151.1
DIR9: IC20.P$19, JP136.4, JP138.4, R168.1
DIR10: IC22.P$19, JP150.4, JP152.4, R185.1
DIR11: IC24.P$19, JP164.4, JP166.4, R202.1
DIR12: IC26.P$19, JP178.4, JP180.4, R219.1
DIR13: IC28.P$19, JP192.4, JP194.4, R236.1
DIR14: IC30.P$19, JP206.4, JP208.4, R253.1
DIR15: IC32.P$19, JP220.4, JP222.4, R270.1
DIR16: IC34.P$19, JP234.4, JP236.4, R287.1
DIR17: IC36.P$19, JP248.4, JP250.4, R304.1
DIR18: IC38.P$19, JP262.4, JP264.4, R321.1
DIR19: IC40.P$19, JP276.4, JP278.4, R338.1
DIR20: IC42.P$19, JP290.4, JP292.4, R355.1
DIR21: IC44.P$19, JP304.4, JP306.4, R372.1
DIR22: IC46.P$19, JP318.4, JP320.4, R389.1
DIR23: IC48.P$19, JP332.4, JP334.4, R406.1
DIR24: IC50.P$19, JP346.4, JP348.4, R423.1
DIR25: IC52.P$19, JP360.4, JP362.4, R440.1
DIR26: IC54.P$19, JP374.4, JP376.4, R457.1
DIR27: IC56.P$19, JP388.4, JP390.4, R474.1
DIR28: IC58.P$19, JP402.4, JP404.4, R491.1
DIR29: IC60.P$19, JP416.4, JP418.4, R508.1
DIR30: IC62.P$19, JP430.4, JP432.4, R525.1
DIR31: IC64.P$19, JP444.4, JP446.4, R542.1
DIR32: IC66.P$19, JP458.4, JP460.4, R559.1
DIR33: IC68.P$19, JP472.4, JP474.4, R576.1
DIR34: IC70.P$19, JP486.4, JP488.4, R593.1
DIR35: IC72.P$19, JP500.4, JP502.4, R610.1
DIR36: IC74.P$19, JP514.4, JP516.4, R627.1
DIR37: IC76.P$19, JP528.4, JP530.4, R644.1
DIR38: IC78.P$19, JP542.4, JP544.4, R661.1
DIR39: IC80.P$19, JP556.4, JP558.4, R678.1
ENABLE: IC1.P$2, JP6.1, JP13.1, R10.1
ENABLE1: IC4.P$2, JP17.1, JP25.1, R31.1
ENABLE2: IC6.P$2, JP31.1, JP39.1, R48.1
ENABLE3: IC8.P$2, JP45.1, JP53.1, R65.1
ENABLE4: IC10.P$2, JP59.1, JP67.1, R82.1
ENABLE5: IC12.P$2, JP73.1, JP81.1, R99.1
ENABLE6: IC14.P$2, JP87.1, JP95.1, R116.1
ENABLE7: IC16.P$2, JP101.1, JP109.1, R133.1
ENABLE8: IC18.P$2, JP115.1, JP123.1, R150.1
ENABLE9: IC20.P$2, JP129.1, JP137.1, R167.1
ENABLE10: IC22.P$2, JP143.1, JP151.1, R184.1
ENABLE11: IC24.P$2, JP157.1, JP165.1, R201.1
ENABLE12: IC26.P$2, JP171.1, JP179.1, R218.1
ENABLE13: IC28.P$2, JP185.1, JP193.1, R235.1
ENABLE14: IC30.P$2, JP199.1, JP207.1, R252.1
ENABLE15: IC32.P$2, JP213.1, JP221.1, R269.1
ENABLE16: IC34.P$2, JP227.1, JP235.1, R286.1
ENABLE17: IC36.P$2, JP241.1, JP249.1, R303.1
ENABLE18: IC38.P$2, JP255.1, JP263.1, R320.1
ENABLE19: IC40.P$2, JP269.1, JP277.1, R337.1
ENABLE20: IC42.P$2, JP283.1, JP291.1, R354.1
ENABLE21: IC44.P$2, JP297.1, JP305.1, R371.1
ENABLE22: IC46.P$2, JP311.1, JP319.1, R388.1
ENABLE23: IC48.P$2, JP325.1, JP333.1, R405.1
ENABLE24: IC50.P$2, JP339.1, JP347.1, R422.1
ENABLE25: IC52.P$2, JP353.1, JP361.1, R439.1
ENABLE26: IC54.P$2, JP367.1, JP375.1, R456.1
ENABLE27: IC56.P$2, JP381.1, JP389.1, R473.1
ENABLE28: IC58.P$2, JP395.1, JP403.1, R490.1
ENABLE29: IC60.P$2, JP409.1, JP417.1, R507.1
ENABLE30: IC62.P$2, JP423.1, JP431.1, R524.1
ENABLE31: IC64.P$2, JP437.1, JP445.1, R541.1
ENABLE32: IC66.P$2, JP451.1, JP459.1, R558.1
ENABLE33: IC68.P$2, JP465.1, JP473.1, R575.1
ENABLE34: IC70.P$2, JP479.1, JP487.1, R592.1
ENABLE35: IC72.P$2, JP493.1, JP501.1, R609.1
ENABLE36: IC74.P$2, JP507.1, JP515.1, R626.1
ENABLE37: IC76.P$2, JP521.1, JP529.1, R643.1
ENABLE38: IC78.P$2, JP535.1, JP543.1, R660.1
ENABLE39: IC80.P$2, JP549.1, JP557.1, R677.1
GND: 3/5V.2, C1.2, C2.2, C7.2, C8.2, C9.2, C10.2, C14.-, IC1.P$3, IC1.P$18, IC1.P$29, JP1.1, JP7.1, JP12.2, JP14.2, PWR_LED.C, R7.1, R10.2, R16.3, R18.1, R19.1, R20.2
GND1: 3/5V1.2, C3.2, C5.2, C12.2, C13.2, C15.2, C17.-, C18.2, IC4.P$3, IC4.P$18, IC4.P$29, JP19.1, JP22.1, JP24.2, JP26.2, PWR_LED1.C, R21.1, R22.3, R23.1, R24.1, R25.2, R31.2
GND2: 3/5V2.2, C19.2, C21.2, C22.2, C23.2, C24.2, C26.-, C27.2, IC6.P$3, IC6.P$18, IC6.P$29, JP33.1, JP36.1, JP38.2, JP40.2, PWR_LED2.C, R38.1, R39.3, R40.1, R41.1, R42.2, R48.2
GND3: 3/5V3.2, C28.2, C30.2, C31.2, C32.2, C33.2, C35.-, C36.2, IC8.P$3, IC8.P$18, IC8.P$29, JP47.1, JP50.1, JP52.2, JP54.2, PWR_LED3.C, R55.1, R56.3, R57.1, R58.1, R59.2, R65.2
GND4: 3/5V4.2, C37.2, C39.2, C40.2, C41.2, C42.2, C44.-, C45.2, IC10.P$3, IC10.P$18, IC10.P$29, JP61.1, JP64.1, JP66.2, JP68.2, PWR_LED4.C, R72.1, R73.3, R74.1, R75.1, R76.2, R82.2
GND5: 3/5V5.2, C46.2, C48.2, C49.2, C50.2, C51.2, C53.-, C54.2, IC12.P$3, IC12.P$18, IC12.P$29, JP75.1, JP78.1, JP80.2, JP82.2, PWR_LED5.C, R89.1, R90.3, R91.1, R92.1, R93.2, R99.2
GND6: 3/5V6.2, C55.2, C57.2, C58.2, C59.2, C60.2, C62.-, C63.2, IC14.P$3, IC14.P$18, IC14.P$29, JP89.1, JP92.1, JP94.2, JP96.2, PWR_LED6.C, R106.1, R107.3, R108.1, R109.1, R110.2, R116.2
GND7: 3/5V7.2, C64.2, C66.2, C67.2, C68.2, C69.2, C71.-, C72.2, IC16.P$3, IC16.P$18, IC16.P$29, JP103.1, JP106.1, JP108.2, JP110.2, PWR_LED7.C, R123.1, R124.3, R125.1, R126.1, R127.2, R133.2
GND8: 3/5V8.2, C73.2, C75.2, C76.2, C77.2, C78.2, C80.-, C81.2, IC18.P$3, IC18.P$18, IC18.P$29, JP117.1, JP120.1, JP122.2, JP124.2, PWR_LED8.C, R140.1, R141.3, R142.1, R143.1, R144.2, R150.2
GND9: 3/5V9.2, C82.2, C84.2, C85.2, C86.2, C87.2, C89.-, C90.2, IC20.P$3, IC20.P$18, IC20.P$29, JP131.1, JP134.1, JP136.2, JP138.2, PWR_LED9.C, R157.1, R158.3, R159.1, R160.1, R161.2, R167.2
GND10: 3/5V10.2, C91.2, C93.2, C94.2, C95.2, C96.2, C98.-, C99.2, IC22.P$3, IC22.P$18, IC22.P$29, JP145.1, JP148.1, JP150.2, JP152.2, PWR_LED10.C, R174.1, R175.3, R176.1, R177.1, R178.2, R184.2
GND11: 3/5V11.2, C100.2, C102.2, C103.2, C104.2, C105.2, C107.-, C108.2, IC24.P$3, IC24.P$18, IC24.P$29, JP159.1, JP162.1, JP164.2, JP166.2, PWR_LED11.C, R191.1, R192.3, R193.1, R194.1, R195.2, R201.2
GND12: 3/5V12.2, C109.2, C111.2, C112.2, C113.2, C114.2, C116.-, C117.2, IC26.P$3, IC26.P$18, IC26.P$29, JP173.1, JP176.1, JP178.2, JP180.2, PWR_LED12.C, R208.1, R209.3, R210.1, R211.1, R212.2, R218.2
GND13: 3/5V13.2, C118.2, C120.2, C121.2, C122.2, C123.2, C125.-, C126.2, IC28.P$3, IC28.P$18, IC28.P$29, JP187.1, JP190.1, JP192.2, JP194.2, PWR_LED13.C, R225.1, R226.3, R227.1, R228.1, R229.2, R235.2
GND14: 3/5V14.2, C127.2, C129.2, C130.2, C131.2, C132.2, C134.-, C135.2, IC30.P$3, IC30.P$18, IC30.P$29, JP201.1, JP204.1, JP206.2, JP208.2, PWR_LED14.C, R242.1, R243.3, R244.1, R245.1, R246.2, R252.2
GND15: 3/5V15.2, C136.2, C138.2, C139.2, C140.2, C141.2, C143.-, C144.2, IC32.P$3, IC32.P$18, IC32.P$29, JP215.1, JP218.1, JP220.2, JP222.2, PWR_LED15.C, R259.1, R260.3, R261.1, R262.1, R263.2, R269.2
GND16: 3/5V16.2, C145.2, C147.2, C148.2, C149.2, C150.2, C152.-, C153.2, IC34.P$3, IC34.P$18, IC34.P$29, JP229.1, JP232.1, JP234.2, JP236.2, PWR_LED16.C, R276.1, R277.3, R278.1, R279.1, R280.2, R286.2
GND17: 3/5V17.2, C154.2, C156.2, C157.2, C158.2, C159.2, C161.-, C162.2, IC36.P$3, IC36.P$18, IC36.P$29, JP243.1, JP246.1, JP248.2, JP250.2, PWR_LED17.C, R293.1, R294.3, R295.1, R296.1, R297.2, R303.2
GND18: 3/5V18.2, C163.2, C165.2, C166.2, C167.2, C168.2, C170.-, C171.2, IC38.P$3, IC38.P$18, IC38.P$29, JP257.1, JP260.1, JP262.2, JP264.2, PWR_LED18.C, R310.1, R311.3, R312.1, R313.1, R314.2, R320.2
GND19: 3/5V19.2, C172.2, C174.2, C175.2, C176.2, C177.2, C179.-, C180.2, IC40.P$3, IC40.P$18, IC40.P$29, JP271.1, JP274.1, JP276.2, JP278.2, PWR_LED19.C, R327.1, R328.3, R329.1, R330.1, R331.2, R337.2
GND20: 3/5V20.2, C181.2, C183.2, C184.2, C185.2, C186.2, C188.-, C189.2, IC42.P$3, IC42.P$18, IC42.P$29, JP285.1, JP288.1, JP290.2, JP292.2, PWR_LED20.C, R344.1, R345.3, R346.1, R347.1, R348.2, R354.2
GND21: 3/5V21.2, C190.2, C192.2, C193.2, C194.2, C195.2, C197.-, C198.2, IC44.P$3, IC44.P$18, IC44.P$29, JP299.1, JP302.1, JP304.2, JP306.2, PWR_LED21.C, R361.1, R362.3, R363.1, R364.1, R365.2, R371.2
GND22: 3/5V22.2, C199.2, C201.2, C202.2, C203.2, C204.2, C206.-, C207.2, IC46.P$3, IC46.P$18, IC46.P$29, JP313.1, JP316.1, JP318.2, JP320.2, PWR_LED22.C, R378.1, R379.3, R380.1, R381.1, R382.2, R388.2
GND23: 3/5V23.2, C208.2, C210.2, C211.2, C212.2, C213.2, C215.-, C216.2, IC48.P$3, IC48.P$18, IC48.P$29, JP327.1, JP330.1, JP332.2, JP334.2, PWR_LED23.C, R395.1, R396.3, R397.1, R398.1, R399.2, R405.2
GND24: 3/5V24.2, C217.2, C219.2, C220.2, C221.2, C222.2, C224.-, C225.2, IC50.P$3, IC50.P$18, IC50.P$29, JP341.1, JP344.1, JP346.2, JP348.2, PWR_LED24.C, R412.1, R413.3, R414.1, R415.1, R416.2, R422.2
GND25: 3/5V25.2, C226.2, C228.2, C229.2, C230.2, C231.2, C233.-, C234.2, IC52.P$3, IC52.P$18, IC52.P$29, JP355.1, JP358.1, JP360.2, JP362.2, PWR_LED25.C, R429.1, R430.3, R431.1, R432.1, R433.2, R439.2
GND26: 3/5V26.2, C235.2, C237.2, C238.2, C239.2, C240.2, C242.-, C243.2, IC54.P$3, IC54.P$18, IC54.P$29, JP369.1, JP372.1, JP374.2, JP376.2, PWR_LED26.C, R446.1, R447.3, R448.1, R449.1, R450.2, R456.2
GND27: 3/5V27.2, C244.2, C246.2, C247.2, C248.2, C249.2, C251.-, C252.2, IC56.P$3, IC56.P$18, IC56.P$29, JP383.1, JP386.1, JP388.2, JP390.2, PWR_LED27.C, R463.1, R464.3, R465.1, R466.1, R467.2, R473.2
GND28: 3/5V28.2, C253.2, C255.2, C256.2, C257.2, C258.2, C260.-, C261.2, IC58.P$3, IC58.P$18, IC58.P$29, JP397.1, JP400.1, JP402.2, JP404.2, PWR_LED28.C, R480.1, R481.3, R482.1, R483.1, R484.2, R490.2
GND29: 3/5V29.2, C262.2, C264.2, C265.2, C266.2, C267.2, C269.-, C270.2, IC60.P$3, IC60.P$18, IC60.P$29, JP411.1, JP414.1, JP416.2, JP418.2, PWR_LED29.C, R497.1, R498.3, R499.1, R500.1, R501.2, R507.2
GND30: 3/5V30.2, C271.2, C273.2, C274.2, C275.2, C276.2, C278.-, C279.2, IC62.P$3, IC62.P$18, IC62.P$29, JP425.1, JP428.1, JP430.2, JP432.2, PWR_LED30.C, R514.1, R515.3, R516.1, R517.1, R518.2, R524.2
GND31: 3/5V31.2, C280.2, C282.2, C283.2, C284.2, C285.2, C287.-, C288.2, IC64.P$3, IC64.P$18, IC64.P$29, JP439.1, JP442.1, JP444.2, JP446.2, PWR_LED31.C, R531.1, R532.3, R533.1, R534.1, R535.2, R541.2
GND32: 3/5V32.2, C289.2, C291.2, C292.2, C293.2, C294.2, C296.-, C297.2, IC66.P$3, IC66.P$18, IC66.P$29, JP453.1, JP456.1, JP458.2, JP460.2, PWR_LED32.C, R548.1, R549.3, R550.1, R551.1, R552.2, R558.2
GND33: 3/5V33.2, C298.2, C300.2, C301.2, C302.2, C303.2, C305.-, C306.2, IC68.P$3, IC68.P$18, IC68.P$29, JP467.1, JP470.1, JP472.2, JP474.2, PWR_LED33.C, R565.1, R566.3, R567.1, R568.1, R569.2, R575.2
GND34: 3/5V34.2, C307.2, C309.2, C310.2, C311.2, C312.2, C314.-, C315.2, IC70.P$3, IC70.P$18, IC70.P$29, JP481.1, JP484.1, JP486.2, JP488.2, PWR_LED34.C, R582.1, R583.3, R584.1, R585.1, R586.2, R592.2
GND35: 3/5V35.2, C316.2, C318.2, C319.2, C320.2, C321.2, C323.-, C324.2, IC72.P$3, IC72.P$18, IC72.P$29, JP495.1, JP498.1, JP500.2, JP502.2, PWR_LED35.C, R599.1, R600.3, R601.1, R602.1, R603.2, R609.2
GND36: 3/5V36.2, C325.2, C327.2, C328.2, C329.2, C330.2, C332.-, C333.2, IC74.P$3, IC74.P$18, IC74.P$29, JP509.1, JP512.1, JP514.2, JP516.2, PWR_LED36.C, R616.1, R617.3, R618.1, R619.1, R620.2, R626.2
GND37: 3/5V37.2, C334.2, C336.2, C337.2, C338.2, C339.2, C341.-, C342.2, IC76.P$3, IC76.P$18, IC76.P$29, JP523.1, JP526.1, JP528.2, JP530.2, PWR_LED37.C, R633.1, R634.3, R635.1, R636.1, R637.2, R643.2
GND38: 3/5V38.2, C343.2, C345.2, C346.2, C347.2, C348.2, C350.-, C351.2, IC78.P$3, IC78.P$18, IC78.P$29, JP537.1, JP540.1, JP542.2, JP544.2, PWR_LED38.C, R650.1, R651.3, R652.1, R653.1, R654.2, R660.2
GND39: 3/5V39.2, C352.2, C354.2, C355.2, C356.2, C357.2, C359.-, C360.2, IC80.P$3, IC80.P$18, IC80.P$29, JP551.1, JP554.1, JP556.2, JP558.2, PWR_LED39.C, R667.1, R668.3, R669.1, R670.1, R671.2, R677.2
MS1: IC1.P$9, JP6.2, JP13.2, R1.1
MS2: IC1.P$10, JP10.1, JP11.1, R2.1
MS3: IC1.P$11, JP10.2, JP11.2, R3.1
MS4: IC4.P$9, JP17.2, JP25.2, R26.1
MS5: IC4.P$10, JP20.1, JP23.1, R27.1
MS6: IC4.P$11, JP20.2, JP23.2, R28.1
MS7: IC6.P$9, JP31.2, JP39.2, R43.1
MS8: IC6.P$10, JP34.1, JP37.1, R44.1
MS9: IC6.P$11, JP34.2, JP37.2, R45.1
MS10: IC8.P$9, JP45.2, JP53.2, R60.1
MS11: IC8.P$10, JP48.1, JP51.1, R61.1
MS12: IC8.P$11, JP48.2, JP51.2, R62.1
MS13: IC10.P$9, JP59.2, JP67.2, R77.1
MS14: IC10.P$10, JP62.1, JP65.1, R78.1
MS15: IC10.P$11, JP62.2, JP65.2, R79.1
MS16: IC12.P$9, JP73.2, JP81.2, R94.1
MS17: IC12.P$10, JP76.1, JP79.1, R95.1
MS18: IC12.P$11, JP76.2, JP79.2, R96.1
MS19: IC14.P$9, JP87.2, JP95.2, R111.1
MS20: IC14.P$10, JP90.1, JP93.1, R112.1
MS21: IC14.P$11, JP90.2, JP93.2, R113.1
MS22: IC16.P$9, JP101.2, JP109.2, R128.1
MS23: IC16.P$10, JP104.1, JP107.1, R129.1
MS24: IC16.P$11, JP104.2, JP107.2, R130.1
MS25: IC18.P$9, JP115.2, JP123.2, R145.1
MS26: IC18.P$10, JP118.1, JP121.1, R146.1
MS27: IC18.P$11, JP118.2, JP121.2, R147.1
MS28: IC20.P$9, JP129.2, JP137.2, R162.1
MS29: IC20.P$10, JP132.1, JP135.1, R163.1
MS30: IC20.P$11, JP132.2, JP135.2, R164.1
MS31: IC22.P$9, JP143.2, JP151.2, R179.1
MS32: IC22.P$10, JP146.1, JP149.1, R180.1
MS33: IC22.P$11, JP146.2, JP149.2, R181.1
MS34: IC24.P$9, JP157.2, JP165.2, R196.1
MS35: IC24.P$10, JP160.1, JP163.1, R197.1
MS36: IC24.P$11, JP160.2, JP163.2, R198.1
MS37: IC26.P$9, JP171.2, JP179.2, R213.1
MS38: IC26.P$10, JP174.1, JP177.1, R214.1
MS39: IC26.P$11, JP174.2, JP177.2, R215.1
MS40: IC28.P$9, JP185.2, JP193.2, R230.1
MS41: IC28.P$10, JP188.1, JP191.1, R231.1
MS42: IC28.P$11, JP188.2, JP191.2, R232.1
MS43: IC30.P$9, JP199.2, JP207.2, R247.1
MS44: IC30.P$10, JP202.1, JP205.1, R248.1
MS45: IC30.P$11, JP202.2, JP205.2, R249.1
MS46: IC32.P$9, JP213.2, JP221.2, R264.1
MS47: IC32.P$10, JP216.1, JP219.1, R265.1
MS48: IC32.P$11, JP216.2, JP219.2, R266.1
MS49: IC34.P$9, JP227.2, JP235.2, R281.1
MS50: IC34.P$10, JP230.1, JP233.1, R282.1
MS51: IC34.P$11, JP230.2, JP233.2, R283.1
MS52: IC36.P$9, JP241.2, JP249.2, R298.1
MS53: IC36.P$10, JP244.1, JP247.1, R299.1
MS54: IC36.P$11, JP244.2, JP247.2, R300.1
MS55: IC38.P$9, JP255.2, JP263.2, R315.1
MS56: IC38.P$10, JP258.1, JP261.1, R316.1
MS57: IC38.P$11, JP258.2, JP261.2, R317.1
MS58: IC40.P$9, JP269.2, JP277.2, R332.1
MS59: IC40.P$10, JP272.1, JP275.1, R333.1
MS60: IC40.P$11, JP272.2, JP275.2, R334.1
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
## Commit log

2013-03-01 addign hardwrae files
    .brd and .sch files added.
2013-03-05 Created production panel
2013-04-17 Silk fix for panel
    updated panel with corrections to silk. Removed version numbers from
    hardware files (version numbers in GitHub tags now).
2013-05-20 Changed Current pot silk
    Chnaged the silkscreen arrow by the current adjustment potentiometer to
    reflect the correct direction.
    CC = less
    C = more
2013-05-28 Production ready v14
    v14 corrects the trimpot silkscreen error that failed to make it into
    v13
2013-06-27 Added Gitignore
    straight up.
2013-06-27 Started v15 revisions
    Changed caps and resis to 0603, updated version number on PCB and
    Schematic, re-routed a few traces. Nowhere near done
2013-06-27 Trace Re-Routes and Mask Changes
    After changing caps/res to 0603 major re-routing happened. Also changed
    the mask settings to make sure the bigger vias were not covered.
2013-06-28 Changed Schematic Nets
    Nets changed to new specifications
2013-06-28 Revert "Changed Schematic Nets"
    This reverts commit ceb7b9bd87dc9e1a8942882cf4505f035ac33b39.
2013-06-28 Trace cleanup
2013-07-01 Revised PLewis's Suggestions
    Spaced the resistors to combat jumpers, revised a few trace angles.
2013-07-01 Drc Angle Check
    Fixed as many DRC angle checks as possible.
2013-07-02 Updated Schematic
    Changed the nets, the previous commit did not sync correctly.
2013-07-10 Frame updated, Angles , Creative Commons added
    Added new schematic framrs, cleaned up some trace angels and added the
    creative commons license.
2013-08-02 Panels
    Created giant panel and normal size panel
2013-08-02 deleted v14 panel
2013-12-11 Updating README
2013-12-11 Update README.md
    Fixing product link typos
2014-03-28 Version 1.6 update -
    * Removed large hole on bottom solder mask (because vias will short out with plane if a metal heatsink is used, this is kinda pointless)
    * Changed R13 to 8.3K to give much more useful range of pot motion
    * Added current limiting resistors to STEP and DIR lines
    * got rid of all angle errors in DRC
    * Added more explanation of R16 current adjust pot behavior in schematic
2014-03-31 Revert "Version 1.6 update -"
    This reverts commit 1063980bfb8b78f8e4fa00b59bbbd0f6b30be38e.
2014-03-31 Updated STEP and DIR inputs schematic net wires so they are not as confusing.
2014-03-31 Added extra bottom silk markings that show grouping for the bottom row of screw terminals.
2014-04-08 Updating part package w/ Sparkle IDs
2014-08-11 Adding 4 layer note to tDocu on board
2014-08-13 changed fiducials to regulars
    also deleted old panels in prep for new ones
2014-08-13 created panel and giant panel
2014-08-27 re-cammed giant panel
    I made a mistake on my first cam job. Forgot that it was a 4-layer
    board. This corrects that and gets the right gerbers to Gold Phoenix.
2014-10-23 Arduija Code
    Gets to home and that's it.
2014-10-23 Arduija
    Home and move working
2014-10-23 Arduija with table
    added Casey's table
2014-10-23 It Works!!!
    Finally got a base of letters and their coordinates to start creating
    messages.
2014-10-27 Ready for public display
    Combined both files into one, added lots of comments, added push button
    to trigger messages so it wouldn't be running the entire time its on
    display. Added more messages.
2015-02-12 Adding in demo sketch for hook-up guide
2015-02-12 Adding README updates for new revision, firmware addition
2015-02-12 Adding in tag info to README
2015-02-12 Update README.md
    Fixing markdown typos
2015-02-13 Adding Arduija demo code
2015-02-13 Fixing repo structure
2015-02-13 Added example sketches from Easy Driver Examples webpage, and added notes to readme.md about SparkFun hookup guide and Easy Driver Example sketches.
2015-03-20 Updating version number to show change in CAM job
2015-03-20 created panels v16a
2015-04-03 Updating IC to proper A4988 device
2016-11-10 Fixing typo in schematic note to proper screw terminal size
2019-06-19 Update SparkFun_Big_Easy_Driver_Basic_Demo.ino
    Updating code to reflect 1000 steps based on description and how programmers start counting from 0 based on the `if()` statement's logic.
